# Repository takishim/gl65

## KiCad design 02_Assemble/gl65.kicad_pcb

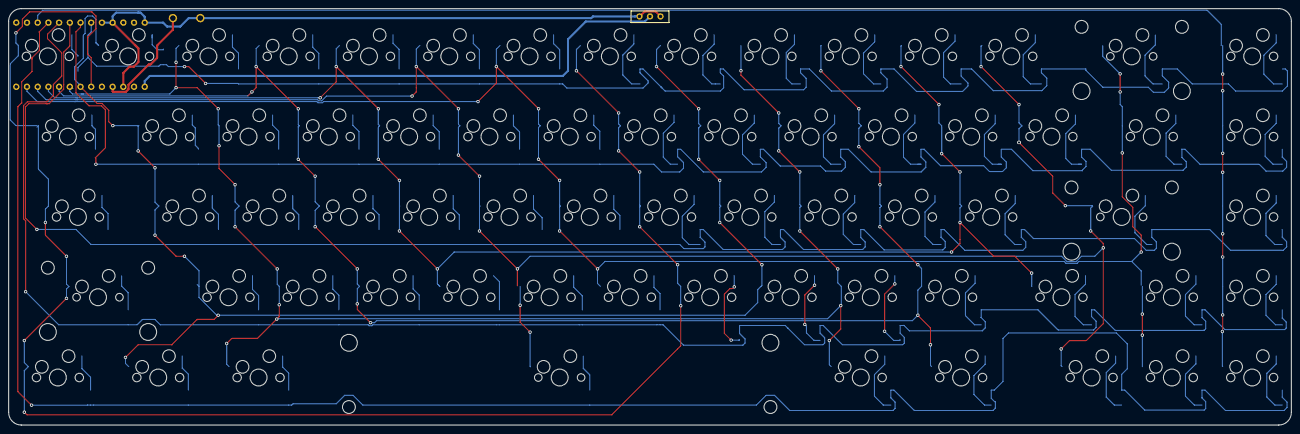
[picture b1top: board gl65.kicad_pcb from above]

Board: 2 copper layers, 304.4 x 98.8 mm, 137 parts (0 on the bottom side), 83 nets.

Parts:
D1, D2, D3, D4, D5, D6, D7, D8, D9, D10, D11, D12, D13, D14, D15, D16, D17, D18, D19, D20, D21, D22, D23, D24, D25, D26, D27, D28, D29, D30, D31, D32, D33, D34, D35, D36, D37, D38, D39, D40, D41, D42, D43, D44, D45, D46, D47, D48, D49, D50, D51, D52, D53, D54, D55, D56, D57, D58, D59, D60, D61, D62, D63, D64, D65, D66, D67: D; Diode_SMD
J1: Conn_01x02; Battery_XH2.5_GL_PCB
SW1, SW2: SW_PUSH; CherryMX_Hotswap_1u_Small1
SW3, SW4, SW5, SW6, SW7, SW8, SW9, SW10, SW11, SW12, SW13, SW15, SW17, SW18, SW19, SW20, SW21, SW22, SW23, SW24, SW25, SW26, SW27, SW28, SW30, SW32, SW33, SW34, SW35, SW36, SW37, SW38, SW39, SW40, SW41, SW42, SW44, SW46, SW47, SW48, SW49, SW50, SW51, SW52, SW53, SW54, SW55, SW57, SW58, SW65, SW66, SW67: SW_PUSH; CherryMX_Hotswap_1u
SW14: SW_PUSH; CherryMX_Hotswap_2u
SW16, SW29: SW_PUSH; CherryMX_Hotswap_1.5u
SW31, SW56: SW_PUSH; CherryMX_Hotswap_1.75u
SW43, SW45: SW_PUSH; CherryMX_Hotswap_2.25u
SW59, SW60, SW61, SW63, SW64: SW_PUSH; CherryMX_Hotswap_1.25u
SW62: SW_PUSH; CherryMX_Hotswap_6.25u_Rev
SW68: SW_PUSH; ResetSW
U1: BLEMicroPro; Micon_BMP_GL

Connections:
Bat+: J1.1, U1.25
Col0: SW1.1, SW8.1, SW16.1, SW23.1, SW31.1, SW38.1, SW45.1, SW52.1, SW59.1, U1.20
Col1: SW2.1, SW9.1, SW17.1, SW24.1, SW32.1, SW39.1, SW46.1, SW53.1, SW60.1, U1.19
Col2: SW3.1, SW10.1, SW18.1, SW25.1, SW33.1, SW40.1, SW47.1, SW54.1, SW61.1, SW63.1, U1.18
Col3: SW4.1, SW11.1, SW19.1, SW26.1, SW34.1, SW41.1, SW48.1, SW55.1, SW64.1, U1.17
Col4: SW5.1, SW12.1, SW20.1, SW27.1, SW35.1, SW42.1, SW49.1, SW56.1, U1.16
Col5: SW6.1, SW13.1, SW21.1, SW28.1, SW36.1, SW43.1, SW50.1, SW62.1, SW65.1, U1.15
Col6: SW7.1, SW14.1, SW22.1, SW29.1, SW37.1, SW51.1, SW57.1, SW66.1, U1.14
Col7: SW15.1, SW30.1, SW44.1, SW58.1, SW67.1, U1.10
GND: J1.2, SW68.2, U1.3, U1.4, U1.23, U1.26
unnamed: D1.2, SW1.2
unnamed: D2.2, SW2.2
unnamed: D3.2, SW3.2
unnamed: D4.2, SW4.2
unnamed: D5.2, SW5.2
unnamed: D6.2, SW6.2
unnamed: D7.2, SW7.2
unnamed: D8.1, SW8.2
unnamed: D9.1, SW9.2
unnamed: D10.1, SW10.2
unnamed: D11.1, SW11.2
unnamed: D12.1, SW12.2
unnamed: D13.1, SW13.2
unnamed: D14.1, SW14.2
unnamed: D15.1, SW15.2
unnamed: D16.2, SW16.2
unnamed: D17.2, SW17.2
unnamed: D18.2, SW18.2
unnamed: D19.2, SW19.2
unnamed: D20.2, SW20.2
unnamed: D21.2, SW21.2
unnamed: D22.2, SW22.2
unnamed: D23.1, SW23.2
unnamed: D24.1, SW24.2
unnamed: D25.1, SW25.2
unnamed: D26.1, SW26.2
unnamed: D27.1, SW27.2
unnamed: D28.1, SW28.2
unnamed: D29.1, SW29.2
unnamed: D30.1, SW30.2
unnamed: D31.2, SW31.2
unnamed: D32.2, SW32.2
unnamed: D33.2, SW33.2
unnamed: D34.2, SW34.2
unnamed: D35.2, SW35.2
unnamed: D36.2, SW36.2
unnamed: D37.2, SW37.2
unnamed: D38.1, SW38.2
unnamed: D39.1, SW39.2
unnamed: D40.1, SW40.2
unnamed: D41.1, SW41.2
unnamed: D42.1, SW42.2
unnamed: D43.1, SW43.2
unnamed: D44.1, SW44.2
unnamed: D45.2, SW45.2
unnamed: D46.2, SW46.2
unnamed: D47.2, SW47.2
unnamed: D48.2, SW48.2
unnamed: D49.2, SW49.2
unnamed: D50.2, SW50.2
unnamed: D51.2, SW51.2
unnamed: D52.1, SW52.2
unnamed: D53.1, SW53.2
unnamed: D54.1, SW54.2
unnamed: D55.1, SW55.2
unnamed: D56.1, SW56.2
unnamed: D57.1, SW57.2
unnamed: D58.1, SW58.2
unnamed: D59.2, SW59.2
unnamed: D60.2, SW60.2
unnamed: D61.2, SW61.2
unnamed: D62.2, SW62.2
unnamed: D63.1, SW63.2
unnamed: D64.1, SW64.2
unnamed: D65.1, SW65.2
unnamed: D66.1, SW66.2
unnamed: D67.1, SW67.2
Reset: SW68.1, U1.22
Row0: D1.1, D2.1, D3.1, D4.1, D5.1, D6.1, D7.1, D8.2, D9.2, D10.2, D11.2, D12.2, D13.2, D14.2, D15.2, U1.5
Row1: D16.1, D17.1, D18.1, D19.1, D20.1, D21.1, D22.1, D23.2, D24.2, D25.2, D26.2, D27.2, D28.2, D29.2, D30.2, U1.6
Row2: D31.1, D32.1, D33.1, D34.1, D35.1, D36.1, D37.1, D38.2, D39.2, D40.2, D41.2, D42.2, D43.2, D44.2, U1.7
Row3: D45.1, D46.1, D47.1, D48.1, D49.1, D50.1, D51.1, D52.2, D53.2, D54.2, D55.2, D56.2, D57.2, D58.2, U1.8
Row4: D59.1, D60.1, D61.1, D62.1, D63.2, D64.2, D65.2, D66.2, D67.2, U1.9

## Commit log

2021-12-30 初期コミット。
2021-12-30 J73GLのデコレージョンテンプレートのaiファイルを追加。
2021-12-30 サリチル酸さんのレビューの指摘を修正。 ・ProMicroの位置を0.3mm下げる ・ResetスイッチをProMicroのすぐ横に移動 ・ソケットのパッドにビアを打たないように変更 ・ダイオードの向きを統一 ・2U以上のキーのリファレンスを表示
